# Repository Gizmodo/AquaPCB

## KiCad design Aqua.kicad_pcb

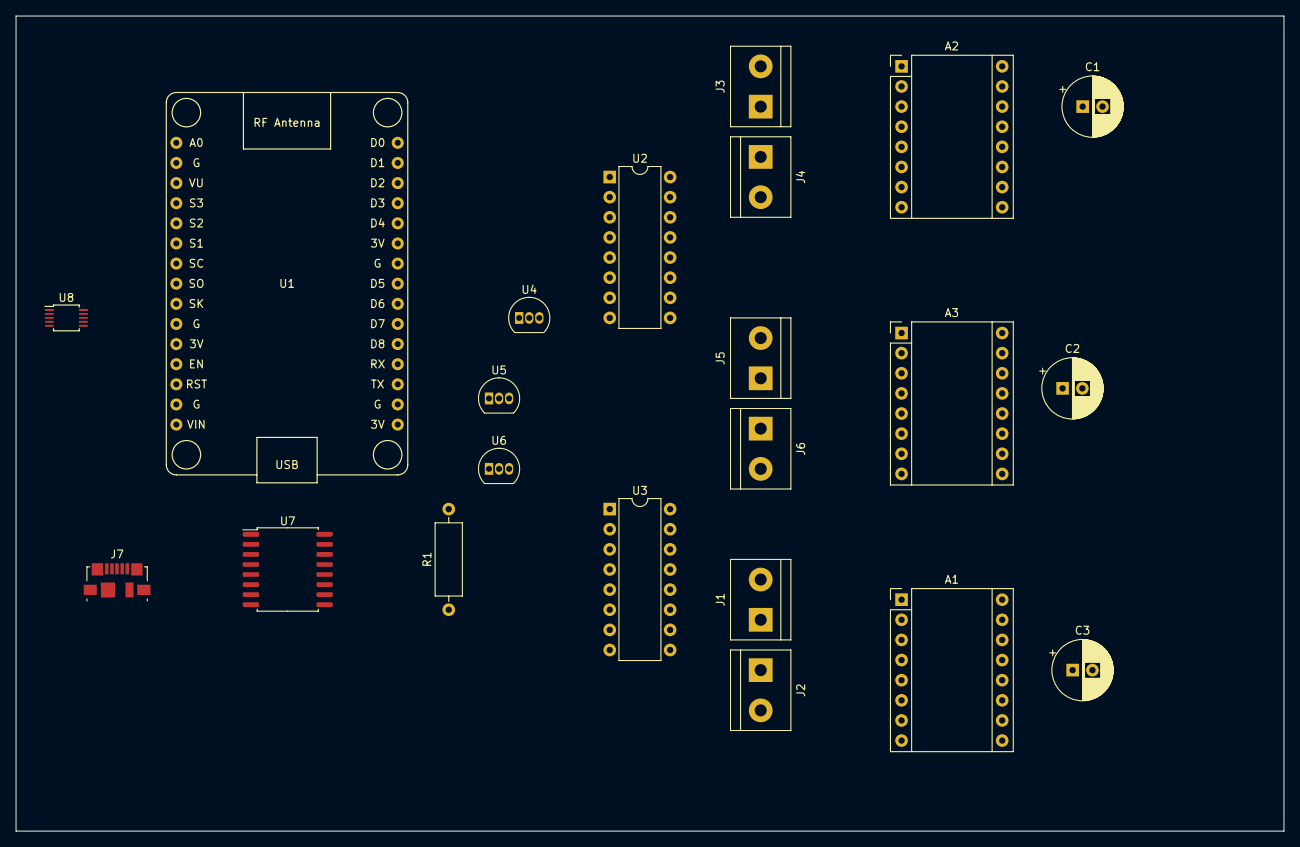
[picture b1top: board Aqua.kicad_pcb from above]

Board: 2 copper layers, 160.0 x 102.9 mm, 22 parts (0 on the bottom side), 27 nets, no tracks yet.

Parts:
A1, A2, A3: Pololu_Breakout_DRV8825; Pololu_Breakout-16_15.2x20.3mm
C1, C2, C3: 0.1mF; CP_Radial_D7.5mm_P2.50mm
J1, J2, J3, J4, J5, J6: Screw_Terminal_01x02; TerminalBlock_bornier-2_P5.08mm
J7: USB_B_Micro; USB_Micro-B_Molex_47346-0001
R1: R4.7K; R_Axial_DIN0309_L9.0mm_D3.2mm_P12.70mm_Horizontal
U1: NodeMCU_1.0_(ESP-12E); NodeMCU1.0(12-E)
U2, U3: 74HC595; DIP-16_W7.62mm
U4, U5, U6: DS18B20; TO-92_Inline
U7: DS3231M; SOIC-16W_7.5x10.3mm_P1.27mm
U8: ADS1115IDGS; TSSOP-10_3x3mm_P0.5mm

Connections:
+3V3: R1.1, U1.16, U2.10, U2.16, U3.10, U3.16, U4.3, U5.3, U6.3, U7.2
+9V: A1.8, A2.8, A3.8, C1.1, C2.1, C3.1
D5: R1.2, U1.23, U4.2, U5.2, U6.2
DATA: U1.22, U2.14
GND: A1.1, A1.7, A2.1, A2.7, A3.1, A3.7, C1.2, C2.2, C3.2, J7.5, U1.10, U1.14, U1.17, U1.24, U2.8, U2.13, U3.8, U3.13, U4.1, U5.1, U6.1, U7.5, U7.6, U7.7, U7.8, U7.9, U7.10, U7.11, U7.12, U7.13, U8.3
unnamed: A1.3, J1.2
unnamed: A1.4, J1.1
unnamed: A1.5, J2.1
unnamed: A1.6, J2.2
unnamed: A1.15, U2.1
unnamed: A1.16, U2.15
unnamed: A2.3, J3.2
unnamed: A2.4, J3.1
unnamed: A2.5, J4.1
unnamed: A2.6, J4.2
unnamed: A2.15, U2.3
unnamed: A2.16, U2.2
unnamed: A3.3, J5.2
unnamed: A3.4, J5.1
unnamed: A3.5, J6.1
unnamed: A3.6, J6.2
unnamed: A3.15, U2.5
unnamed: A3.16, U2.4
unnamed: U1.27, U7.16
unnamed: U1.28, U7.15
unnamed: U2.9, U3.14
VIN: J7.1, U1.15

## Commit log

2020-05-12 Добавлены файлы
2020-05-12 Обновлен gitignore файл
